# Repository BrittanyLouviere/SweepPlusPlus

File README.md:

# Sweep++
 A custom keyboard inspired by the Ferris Sweep layout but with an extra row on top, 2 more thumb keys, and 2 keys dedicated to layer switching beneath each MCU.

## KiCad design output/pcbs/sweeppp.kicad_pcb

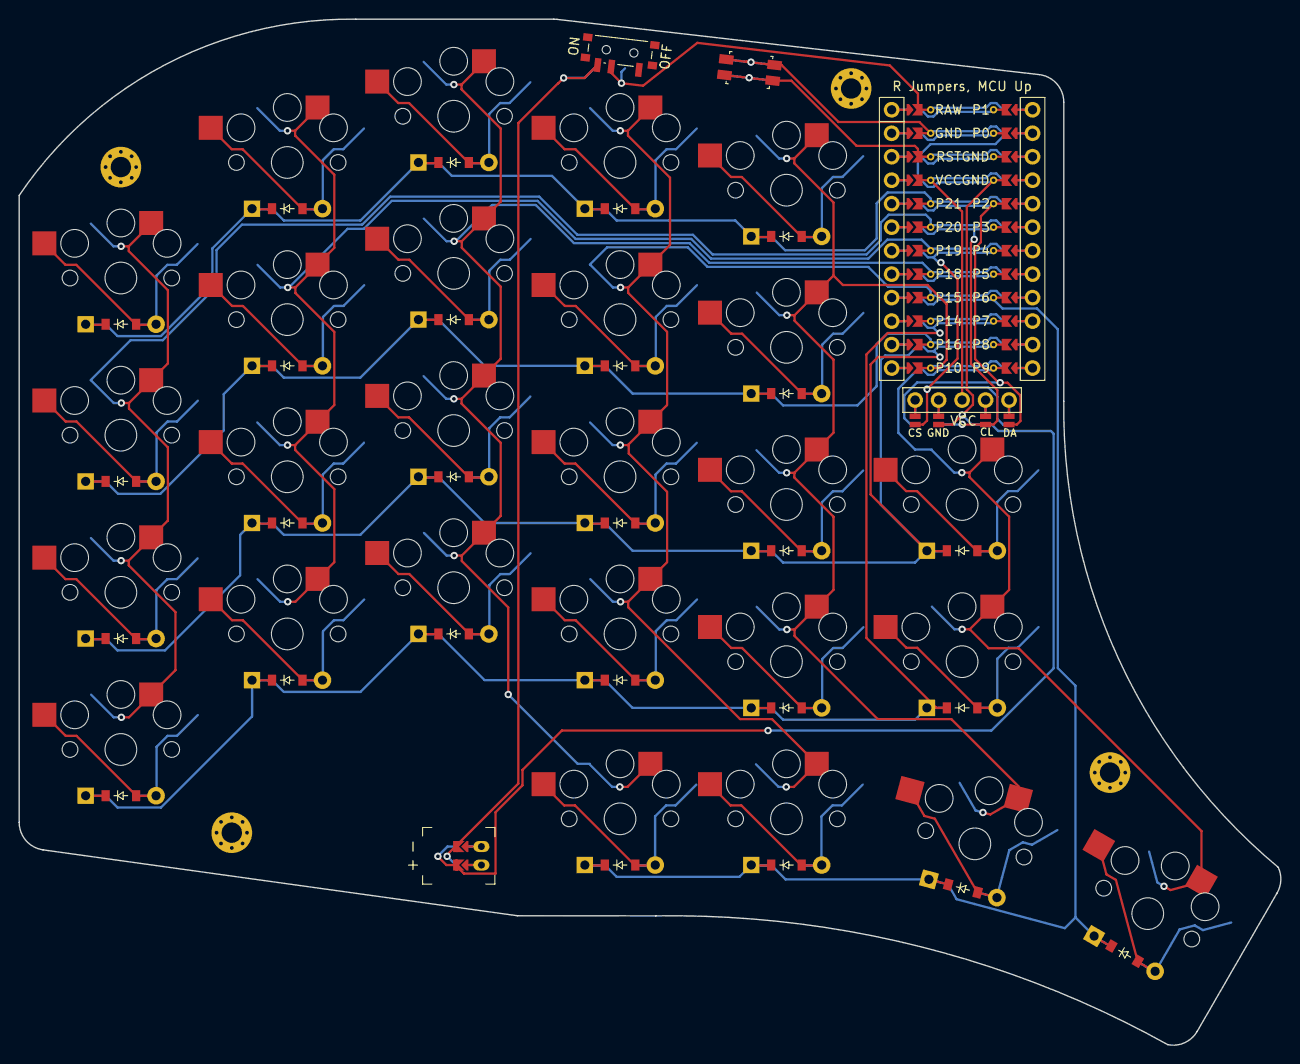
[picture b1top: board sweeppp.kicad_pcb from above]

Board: 2 copper layers, 136.5 x 111.0 mm, 61 parts (0 on the bottom side), 51 nets.

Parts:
D1, D2, D3, D4, D5, D6, D7, D8, D9, D10, D11, D12, D13, D14, D15, D16, D17, D18, D19, D20, D21, D22, D23, D24, D25, D26: ComboDiode
DISP1: display_nice_view
JST1: battery_connector_jst_ph_2
MCU1: mcu_nice_nano
PWR1: power_switch_smd_side
RST1: reset_switch_smd_side
S1, S2, S3, S4, S5, S6, S7, S8, S9, S10, S11, S12, S13, S14, S15, S16, S17, S18, S19, S20, S21, S22, S23, S24, S25, S26: PG1350
_1, _2, _3, _4: MountingHole_2.2mm_M2_Pad_Via

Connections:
BAT_P: JST1.1, PWR1.1, PWR1.3
DISP1_1: DISP1.1, DISP1.14, DISP1.27
DISP1_2: DISP1.2, DISP1.15, DISP1.26
DISP1_4: DISP1.4, DISP1.16, DISP1.25
DISP1_5: DISP1.5, DISP1.17, DISP1.24
GND: DISP1.11, DISP1.21, JST1.2, MCU1.103, MCU1.104, MCU1.123, RST1.1, RST1.3
JST1_1: JST1.11, JST1.21, JST1.31
JST1_2: JST1.12, JST1.22, JST1.32
P2: DISP1.13, DISP1.23, MCU1.105
P3: DISP1.12, DISP1.22, MCU1.106
P4: DISP1.10, DISP1.20, MCU1.107
P6: D23.1, D24.1, D25.1, D26.1, MCU1.109
P7: D1.1, D5.1, D9.1, D13.1, D17.1, D21.1, MCU1.110
P8: D2.1, D6.1, D10.1, D14.1, D18.1, D22.1, MCU1.111
P9: MCU1.112, S21.1, S22.1, S26.1
P10: MCU1.113, S17.1, S18.1, S19.1, S20.1, S25.1
P15: MCU1.116, S13.1, S14.1, S15.1, S16.1, S24.1
P16: D3.1, D7.1, D11.1, D15.1, D19.1, MCU1.114
P18: MCU1.117, S9.1, S10.1, S11.1, S12.1, S23.1
P19: MCU1.118, S5.1, S6.1, S7.1, S8.1
P20: MCU1.119, S1.1, S2.1, S3.1, S4.1
P21: D4.1, D8.1, D12.1, D16.1, D20.1, MCU1.120
RAW: MCU1.124, PWR1.2
RST: MCU1.122, RST1.2, RST1.4
VCC: DISP1.3, MCU1.121
home_cluster: D25.2, S25.2
index_bottom: D13.2, S13.2
index_home: D14.2, S14.2
index_num: D16.2, S16.2
index_top: D15.2, S15.2
inner2_bottom: D21.2, S21.2
inner2_home: D22.2, S22.2
inner_bottom: D17.2, S17.2
inner_cluster: D26.2, S26.2
inner_home: D18.2, S18.2
inner_num: D20.2, S20.2
inner_top: D19.2, S19.2
middle_bottom: D9.2, S9.2
middle_home: D10.2, S10.2
middle_num: D12.2, S12.2
middle_top: D11.2, S11.2
outer2_cluster: D23.2, S23.2
outer_cluster: D24.2, S24.2
pinky_bottom: D1.2, S1.2
pinky_home: D2.2, S2.2
pinky_num: D4.2, S4.2
pinky_top: D3.2, S3.2
ring_bottom: D5.2, S5.2
ring_home: D6.2, S6.2
ring_num: D8.2, S8.2
ring_top: D7.2, S7.2

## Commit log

2024-08-17 Added pinout pics
2024-08-17 Move images to folder
2024-08-17 Added todos
2024-08-17 generated files
2024-08-17 Added nice! footprints
2024-08-17 changed yaml filename
2024-08-17 switched to nice nano and nice view
2024-08-17 fixed nets
2024-08-17 shift nice nano and nice view
2024-08-18 moved the reset button and power switch adjusted outline
2024-08-18 moved jstph
2024-08-18 Added mounting holes
2024-08-18 Added pins for nice!view
2024-08-19 Created bottom case
2024-08-19 Created top case
2024-08-20 Added cutout for microcontroller for case top
2024-08-20 adjusted switch cutout size
2024-08-20 Switched mcu cutout with screen cutout
2024-08-20 Adjusted inner2 column to align with screen
2024-08-24 Formatting cleanup
2024-08-29 Switched to a different nice!nano footprint
2024-08-29 Changed choc footprint
2024-08-29 Routed pcb
2024-08-29 switched to reversible nice!view
2024-08-30 Switch to reversible footprints for jstp, switch, and button
2024-08-30 Removed unused footprints
2024-09-01 moved jst
2024-09-01 Made sure screw holes lined up
2024-09-01 Added traces
2024-09-01 Generated gerbers
2024-09-13 Added screenshot of pcb
2024-09-13 Added arcs to pcb
2024-10-12 Generate new gerbers
2024-11-30 cadquery start
2025-01-15 Getting keypoints
2025-01-16 fixed spacing
2025-01-18 figured out rotation moved logic to function
2025-01-18 key points now generated
2025-01-19 trying a different approach
2025-02-08 Fixed display labels
